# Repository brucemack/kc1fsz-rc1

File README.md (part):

Overview
========

This is a basic two-radio repeater controller that can be used 
to create an amateur or GMRS repeater site. Our goal is to implement
as much of the repeater functionality in software as 
possible. For this reason, we call this the "Software 
Defined Repeater Controller" (SDRC) project. This Github
repo contains the source code for the controller and the 
KiCad design files for the hardware.

The hardware is on two boards. The radio interface board is on the left
and the digital control board is on the right. The digital control board
is mostly a Pico Pi 2. (To avoid any confusion: the Pico is an ARM Cortex-M33 microcontroller. This _is not_ a Linux system like you'd find on a full 
a Raspberry Pi single-board computer).

One of the advantages of an all-digital architecture is that integration
with other digital-voice technologies should be seamless. Please
see the related project called [MicroLink](https://github.com/brucemack/microlink) which
provides a compact EchoLink implementation. Soon the SDRC and MicroLink
systems will be integrated. Reverse-engineering of the D-Star/DMR protocols
will also enable direct integration of those modes at some point. 

Much of the hardware used in traditional analog repeater controller 
designs
(analog cross-point switches, FPGAs, custom DTMF/CTCSS tone detection chips, 
digital voice CODECs, voice delay modules, M7716 noise squelch ICs, AGC circuits, etc.) will not be necessary
if these functions can be performed in software.

A [users guide is provided here](docs/users.md).

The SDRC system was developed by Bruce MacKinnon (KC1FSZ) with extensive design 
input from Dan Brown (W1DAN) of the Wellesley Amateur Radio Society (W1TKZ).
Please reach out with any questions/suggestions.

Capabilities
============

This repeater controller development is in process. The prototype is undergoing bench testing at the moment. We plan to install it at our W1TKZ repeater site within the next month.

Key capabilities of the software so far:

* Support for two receivers and two transmitters. Radios
can operate independently or can be linked to support
remote receiver or cross-band repeater operation.
* Hardware COS and CTCSS inputs for each radio. Positive
and negative logic are supported.
* An optically-isolated hardware PTT output for each radio.
* Optional soft CTCSS (PL) tone encoding and decoding, with support 
for independent tone frequencies for each transmitter/receiver.
* Optional noise squelch using a bi-level system similar to 
the Motorola M7716 IC.
* CW-ID generation.
* Configurable hang time.
* Configurable courtesy tone generation.
* Timeout and lockout with configurable times.
* Optional digital voice ID and other prompts.
* Soft RX/TX gain control adjustable remotely.
* <=250ms digital audio delay to avoid squelch tails.
* Optional AGC control with configurable level target, gain limits, 
and attack/decay parameters.
* Soft DTMF decoding, with password-protected remote commands.
* "Soft console" via USB-connected computer computer with
serial terminal provides a configuration shell and live display of the following:
  - Carrier detect (COS) status
  - PL tone detect (CTCSS) status
  - Push-to-talk (PTT) status
  - Receive/transmit audio level RMS and peak
* Microcontroller uses a watchdog timer to limit the risk of lockup.
* (In development) Remote firmware update via LoRa connection.

Other things to know:

* The audio output range is around 1.25Vpp into 600 ohms.
* The the receiver discriminator input is high impedance.
* Hardware gain adjustments (pots) are used to calibrate dynamic range 
during initial installation.
* The controller runs on +12VDC power input.
* A DB25 connection is used for radio interfaces.
* Over-voltage protection is provided on the audio and logic inputs.
* Over-voltage, reverse-polarity, and transient spike protection is provided
on the power input.

Hardware specs:

* Microcontroller is the RP2350 running at 125 MHz.
* ADC/DACs run at 32k samples/second with 24-bits of
resolution which is more than enough for an analog FM repeater.
* Low-noise op amps are used for audio scaling (TLV9152).
* During testing of the prototype board it was determined that the 
controller consumes ~105mA when idling and ~135mA when repeating. These are
fairly low current consumptions that indicate the the controller may 
be relevant in solar/battery installations.

More documentation:

* A demonstration video of the current prototype 
[can be seen here](https://www.youtube.com/watch?v=HBwrpokd7FI).
* A demonstration video of the soft console [can be seen here](https://www.youtube.com/watch?v=gWjOw0UzMgY).
* The schematic for the main radio interface board [is here](https://github.com/brucemack/kc1fsz-rc1/blob/main/hw/if-2/plots/if-2.pdf).
* The schematic for the microcontroller board [is here](https://github.com/brucemack/kc1fsz-rc1/blob/main/hw/digital-2/plots/digital-2.pdf).
* The hardware project for the LoRa integration [is here](https://github.com/brucemack/lora-r2).
* The software project for the LoRa integration [is here](https://github.com/brucemack/remote-probe).

Credit/Thanks
=============

I've received help from a lot of smart people on this project who have been very generous with their time:

* Dan Brown W1DAN, former president of the Wellesley Club.
* Tom Kinahan N1CPE, trustee of the W1TKZ repeater system.
* Leandra MacLennan AF1R
* Steve Kondo K1STK
* George Zafiropoulos KJ6VU. Among other things, George [sells his own commercial repeater controllers](https://www.packtenna.com/repeaters.html#/). 
* Jim Aspinwall NO1PC.  Jim is very experienced with repeaters and has engineered/maintained several multi-site systems. His [website is very interesting](https://www.no1pc.org/).
* Jeff Otterson (N1KDO), of [NHRC Repeater Controller](https://www.nhrc.net/). 

Legal/License
=============

This work is being made available for non-commercial use by the amateur radio community. Redistribution, commercial use or sale of any part is prohibited.

The hardware for this project is published under the terms of [The TAPR Open Hardware License](https://tapr.org/the-tapr-open-hardware-license).

The software for this project is published under the terms of [GNU GENERAL PUBLIC LICENSE](https://www.gnu.org/licenses/gpl-3.0.en.html).

Technical/Design Notes
======================

Typical Radio Audio Levels and Impedance 
----------------------------------------

I got these comments from an experienced expert:

> ... we usually run the internal audio at a nominal 1v p/p for full system deviation.  That seems to have worked fine.  At the edges you may need more of a voltage swing especially on the output depending on the transmitter you are driving but this covers 90%++ of the cases.

> Discriminator / modulator audio inputs are never 600 Ohms.  The output impedance of the receiver is higher.  Often 5k to 10k Ohms, the modulator inputs are typically low impedance which is fine for an op amp output.  Both unbalanced.

Op Amp Notes
------------

* [TLV9152](https://www.ti.com/lit/ds/symlink/tlv9152.pdf?ts=1750522536760) - Suggested by Dan, output rail-to-rail. This is the part that is in the current design.
* [TL072]() - Output to within +/- 1.5V (typ) of rail. A good part,
but very old. Used in initial prototypes.
* [LMC660](https://www.ti.com/lit/ds/symlink/lmc662.pdf) - Used in SCOM-7K, output rail-to-rail, can drive +/- 18mA.  Characterized as 4.6 to 0.3 output swing with R<sub>L</sub> = 600 ohms. A quad device, not a good choice.
* [TS952](https://www.st.com/content/ccc/resource/technical/document/datasheet/b8/ac/21/72/20/a7/4d/ea/CD00001338.pdf/files/CD00001338.pdf/jcr:content/translations/en.CD00001338.pdf) - Used in the SCOM 7330, output close to rail-to-rail with R<sub>L</sub> = 600 ohms.
* [TLV2462](https://www.ti.com/lit/ds/symlink/tlv2462-q1.pdf?ts=1750512090542) - Output rail-to-rail, can drive +/- 80mA. Noise 11nV/RHz.

Zener Biasing for Single Supply Op Amps
---------------------------------------

From [Analog Devices application note AN-581](https://www.analog.com/en/resources/app-notes/an-581.html):

A Zener should be chosen that has an operating voltage close to Vs/2. Resistor RZ needs to be selected to provide a high enough Zener current to operate the Zener at its stable rated voltage and to keep the Zener output noise low. It is also important to minimize power consumption (and heating) and to prolong the life of the Zener. As the op amp’s input current is essentially zero, it’s a good idea to choose a low power Zener. A 250 mW device is best but the more common 500 mW types are also acceptable. The ideal Zener current varies with each manufacturer but practical IZ levels between 5 mA (250 mW Zener) and 5 µA (500 mW Zener) are usually a good compromise for this application.

Overview of Digital Audio Flow
------------------------------

This diagram shows the flow between one receiver and one
transmitter. Keep in mind that multiple instances of 
this flow are running in parallel for each receiver/transmitter
pair. Furthermore, transmit audio can select/mix from
any of the receivers.

The letters in the diagram above will be referenced throughout.

Generation of I2S Clock/State Machines
--------------------------------------

The PICO PIO (programmable IO) feature has been leveraged
to generate the I2S clock lines and internal state machines.
To save GPIO pins, the same I2S clocks (SCLK, BCLK, LRCLK) are 
shared by the ADC **and** DAC chips.  

Analog to Digital Conversion
----------------------------

The ADC is a TI PC1804 (Flow diagram ref A). This was selected 
because of its simplicity,
availability, and ease of soldering. This is a 24 bit converter
so full scale runs from +/- 8,388,608. The digital interface 
is I2S.

The converter supports a range of conversion rates from 32k
to 192k.  The lowest possible rate has been selected for this
project.

This converter IC has two important filters built-in:
* A low-pass
anti-aliasing filter with a cutoff frequency of f<sub>s</sub>/2.
* A high-pass filter just above 0Hz for DC removal. Testing
has shown that this filter is sharp and doesn't attenuate
the very low audio frequencies used for CTCSS/PL tones.

Decimation From 32k to 8k Audio
-------------------------------

The ADC runs at a sample rate of 32k.  In order to 
reduce memory and CPU requirements the audio stream is down-sampled
to 8k (decimation by 4). See flow diagram reference C and D. 
Following the decimation,
audio processing in the rest of the flow will run at 8k.

This decimation happens in two ÷2 steps. Each decimation step
also includes a half-band LPF so the decimation has 
the effect of band-limiting the audio to 4kHz.

The design process for creating these half-band low-pass
decimation filters is very standard. A detailed discussion 
can be found in section 5.3 (first ed) of the Lyons DSP book.

The cut-off frequency of the first decimation is 8kHz and the 
second is 4kHz.  However, the f<sub>s</sub> of the first 
filter is twice the second so the same filter coefficients
can be used for both decimation steps. I am using a 41-tap 
filter for this process because the transition doesn't need
to be extremely sharp.

Receiver CTCSS/PL Tone Filtering
---------------------------------

The received CTCSS/PL tone needs to be filtered away so that it 
isn't repeated.  This is particularly
important for cross-band repeaters where the *PL tone might 
be different* on the two sides of the repeater.
"Pass-through" CTCSS tone is not desired. If the CTCSS encoder 
is enabled the appropriate tone will be synthesized and added
back to the transmitted signal on the way out.

A [commercial high-pass filter for CTCSS rejection](https://www.masterscommunications.com/products/filter/plf15.html) created by K3KKC and characterized in this
[review by WA1MIK](https://www.masterscommunications.com/products/filter/fl10-eval/fl10-evaluation.html) includes some specifications that can be 
used to guide the design. This filter has a 350Hz 
-3dB frequency and 30dB per octave of steepness.  That's down 
about -68dB at 50Hz. There is a response curve provided
in the WA1MIK article.

K3KKC's filter is analog, but this is a software-defined controller so 
I am replicating this filter behavior using a digital FIR filter 
that is synthesized using the "optimal" (Parks McClellan) algorithm. 
I'm going to assume the transition band starts at 200 Hz (i.e. the 
end of the stop band) and ends at 350 Hz (i.e. the start of the 
pass band). See flow diagram reference F.

We can estimate the number of taps required to perform this
filtering task 
using the so-called "Harris Approximation" (see *Multirate Signal Processing for Communication Systems*, Fredric J. Harris, 2004, page 216, equation (8.16)).

taps = (f<sub>s</sub> / Δf) * (dB<sub>att</sub> / 22)

where dB<sub>att</sub> is the desired attenuation of the stopband
and Δf is the desired width of the transition band.

Using Δf of (375-200) = 175 Hz and dB<sub>att</sub> of 
-68dB, we end up with a requirement of about 141 taps. Unfortunately,
it turns out that my [Parks McClellan implementation](https://github.com/brucemack/firpm-py) is limited to 127 taps at the moment, so
we'll just assume that is close enough. I'll fix that later
if it seems like this matters.

The group-delay of an FIR filter is approximately:

samples<sub>delay</sub> = (N - 1) / 2 

So this filter introduces about 8ms of delay into the system.

Here's a plot of the frequency response of the 127-tap filter
created by the PM algorithm created using Matplotlib:

As a sanity check I ran a 200 Hz tone through the
synthesized filter (amplitude 
1.0) and plotted the output. The amplitude of the output is about 0.0025,
or about -52dB, so things look pretty good on the low end of the
transition band.

As another sanity check I ran a 350 Hz tone through the same
filter and plotted the output. The amplitude is about 0.9, or about 
-0.9dB, so the high end of the transition is looking reasonable as
well.

This 127 tap filter should work fine for the purposes of CTCSS
filtering.

CTCSS Tone Decoder
------------------

See flow diagram reference G.

This is a fairly straight-forward tone detection problem. The 
digital [Goertzel algorithm](https://en.wikipedia.org/wiki/Goertzel_algorithm) is
used to efficiently detect the configured tone in firmware.
Configurable debounce times are used to prevent false triggers
and false drops of the detector.

The algorithm has been tested to ensure sharpness of the 
detection filter. The filter was set to detect the PL 
tone of 123 Hz (W1TZK VHF tone) and a range of tones (plus a 
high level of additive white Gaussian noise) were played
into the filter. The response is charted below. 

One challenge creating a narrow tone detector using the 
Goertzel algorithm is making sure that we are using 
enough samples to provide sufficient frequency resolution.
On the other hand, we want to make sure to provide some 
tolerance for transmitters that are off a bit in their 
PL tone synthesis.

The width of a frequency bucket using any DFT-based 
analysis method is:

BW<sub>bin</sub> = f<sub>s</sub> / samples

The current implementation is using 512 samples (8x 8ms blocks),
which implies a resolution bandwidth of about 15Hz. This also 
implies that the "attack" time of the CTCSS decoder
is about 64ms.

Demonstration Files of My CTCSS Detector Implementation
-------------------------------------------------------

I've created a demonstration of the soft CTCSS decoder in 
action. I've made a 7 second sample clip that consists of 
three parts:
* 2 seconds of white noise
* 3 second of voice audio with a 123 Hz PL tone added (-20dB),
low-pass filtered to 2.3kHz.
* 2 seconds of white noise

The first clip is here: [Sound 2](https://github.com/brucemack/kc1fsz-rc1/raw/refs/heads/main/docs/clip-2.wav). This
is the raw sample.  As expected, you
hear the noise before and after the voice audio - the 
CTCSS tone is ignored. If you listen closely to this clip 
you can also hear the 123 Hz tone under the voice audio. 

The second sound clip is here: [Sound 2b](https://github.com/brucemack/kc1fsz-rc1/raw/refs/heads/main/docs/clip-2b.wav). This
is the sample played through the controller firmware 
with the CTCSS decoder enabled and the CTCSS high-pass filter enabled. Here the noise is blocked
except for a short tail at the end of the voice. The decoder takes about
32ms (around 4 cycles of the PL tone) to determine that 
the tone has stopped. The noise is blocked and the PL 
tone is filtered out. This is close to what we would expect 
a "real" system to sound like.

This test was repeated with the PL tone under the 
voice section of the clip down another 
-6dB for a total of -26dB relative to full-scale (0.05 
amplitude in linear units).  The original clip is here: [Sound 3](https://github.com/brucemack/kc1fsz-rc1/raw/refs/heads/main/docs/clip-3.wav) and the clip played through the controller firmware 
with CTCSS decoder and CTCSS HPF enabled is here: [Sound 3b](https://github.com/brucemack/kc1fsz-rc1/raw/refs/heads/main/docs/clip-3b.wav).

CTCSS Tone Encoder
------------------

See flow diagram reference J. The digital CTCSS generator runs in 
the 8kHz part of the audio flow. Each radio has its
own encoder frequency to support multi-tone systems.

Dan suggested that the goal should be to create a PL tone modulated at about 10% total deviation. If we assume that CW/courtesy tones are generated at a level of between
-14dB and -10dB of full DAC full scale, the PL tone should be 
another -12dB down, or 0.32 * 0.25 = 0.08 linear scale.

Here's a clip with the CTCSS encoder enabled (123 Hz) and 
set to a high 
level (-20dB) so it can be heard: [Sound 3d](https://github.com/brucemack/kc1fsz-rc1/raw/refs/heads/main/docs/clip-3d.wav).

Here's a view of the spectrum with the CTCSS encoder enabled
at 123 Hz under an audio clip:

CW Generator
------------

See flow diagram reference K.

This component is used to generate tones for CW-ID and the 
courtesy tones. Envelope shaping is used to avoid high 
frequency glitches associated with on/off keying.

Voice Synthesis
---------------

See flow diagram reference K.

To reduce storage, voice prompts are compressed using the 
GSM 0610 full-rate CODEC. [I created a fixed-point implementation](https://github.com/brucemack/gsm-0610-codec) of 
this CODEC as part of my [Echolink Implementation](https://github.com/brucemack/microlink). GSM 0610 runs at 8k so this 
is a smooth integration. 

One second of audio requires 8K of flash storage (640 byte
frames transferred at 12.5 frames/second). About
512K of flash has been allocated to voice storage, so 
we've got room for about 60 seconds of recording.

(More to be documented)

Noise Squelch IC From Motorola
------------------------------

Not all radios have access to a reliable COS signal and some 
radios may have inferior noise squelches. There are a few 
ways to deal with this. Jim NO1PC made me aware of an 
interesting component introduced in the Motorola MICOR stations of 
the 1970's to address this challenge. 

The goal of these circuits is to identify the end of a 
transmission as quickly as possible and to squelch (mute) the 
transmitter before the "static crash" is broadcast. If this
detection can be made quickly enough we can avoid the need
to create delayed versions of the receive audio stream.
More on the topic of delay is provided in a later section.

It turns out that Motorola created a custom IC to address
this need.  The IC is called either the M7716 or the M6709, 
or sometimes the SC7716. The IC implements something called
"switched hysteresis squelch."

The Repeater Builder site has a few different articles that 
go into the details of this chip.
* [This article by WAØAUQ](https://www.repeater-builder.com/micor/micor-bi-level-squelch-circuit.html) gives a good overview.
* [This article by W3KKC](https://www.repeater-builder.com/micor/micor-bi-level-squelch-theory.html) also provides some theory.
* [The most detailed article is by Robert W. Meister WA1MIK](https://www.repeater-builder.com/micor/m6709-info/m6709-info.html). Robert
has done a reverse engineering of the chip in order to quantify 
it's behavior.

Quoting from WA1MIK's analysis, a _"noise squelch systems must ignore signals in the voice frequency range of about 300 to 3400 Hz. All of the high-pass filtering is designed to eliminate any voice energy and only look at the noise energy above 
about 5 kHz."_ Conceptually, a "quieted" FM channel would contain 
most of its energy concentrated in the voice band, whereas noise is broadband. 

And from W3KKC's article: _"If the received quality of the input 
signal provides at least 20 dB quieting, (above 1 uV on properly 
working receiver), the IC's logic circuit gives immediate audio 
shut-off, and no squelch tail. If the signal is below 20 dB 
quieting, (below 1 uV, or having some noise), there is a squelch 
tail of 150 milliseconds, long enough so there is no audio 
chopping under "flutter" conditions ..."_. The chart entitled "M6709 Squelch Tail Threshold" in the WA1MIK analysis article summarizes 
this bi-level behavior on the squelch tail.

There are a few things that I'm assuming from these articles, 
although not explicitly stated:

* When the articles talk about "20dB of quieting," I'm pretty
sure this is referring to a measurement of the ratio between 
the voice-band energy (<4kHz) to the above-voice-band energy (>5kHz). Since there is always output coming from an FM discriminator, the 
only way to determine
if that discriminator output is a signal is to determine 
when the noise part of the spectrum has quieted down sufficiently.
* From the WA1MIK tail threshold chart, I am assuming that 
the 10dB of quieting is the threshold for opening the squelch.
* The articles use the term "hysteresis" when describing 
the M7716's functionality. It's not explicitly stated where
the hysteresis loop manifests itself. I am assuming that this
is referring to the fact that the mute to unmute transition 
is immediate but the unmute to mute 
transition is delayed by 150ms (configurable) in the case that a <20dB quieted
signal is lost.
* For example, I am assuming that a transition from 9dB of 
quieting to 21dB and back to 9dB
would result in the squelch immediately opening and
then immediately closing, without delay or asymmetry.
* I am also assuming that if the signal goes above 10dB at any 
time during
the 150ms delay period that the delay counter is reset and
will start to count down again once the signal dips below
10dB of quieting again.

Technical Notes on My Implementation of a Noise Detector
--------------------------------------------------------

Given the theory about the M7716 above, we need to have
a measure of the noise energy present in an input signal.
This is a place where having an overly-wide (32kHz) ADC 
sampling rate is a good thing. 

A high-pass filter is used to extract the energy above
5kHz (see flow diagram reference B). Assuming the transition 
band of this filter starts 
at 4kHz and ends at 6kHz and -30dB of attenuation is 
sufficient, the Harris Approximation tells us to use a 
21-tap FIR filter.

This FIR filter runs directly on the 32kHz sampled
audio from the ADC. Every 10ms an RMS level is computed
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
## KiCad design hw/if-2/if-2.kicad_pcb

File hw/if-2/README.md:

## Audio Input Network Simulation

Simulated audio input network. The trim pot is set to half range.

Frequency response. We are using an ADC with a differential input so a differential gain is plotted:

Frequency response focusing on the range from 60 Hz to 2 kHz. This range is important since we will
be decoding sub-audible CTCSS tones and we want to make sure they are passed into the ADC. The lowest
tone (66 Hz) is only attenuated by about 0.3 dB vs the audible range starting at 200 Hz.

## Audio Output Network Simulation

This is the final filter in the audio output chain. The trim pot is set to half range. A low-pass network is used to suppress noise. This is not used for pre-/de-emphasis.

CTCSS tones need to pass through this network so very low frequency response is necessary.

The gain is provided in case the full-scale DAC amplitude isn't enough to drive the audio input of the radio.  

Simulated audio output network (stage 2):

Frequency response:

Frequency response focusing on the range from 60 Hz to 2 kHz. The lowest tone is only attenuated by about 0.6 dB vs. the audible range. This should be fine.

## ADC Testing at Low Audio Frequency

(To Follow)

## DAC Testing at Low Audio Frequency

(To Follow)

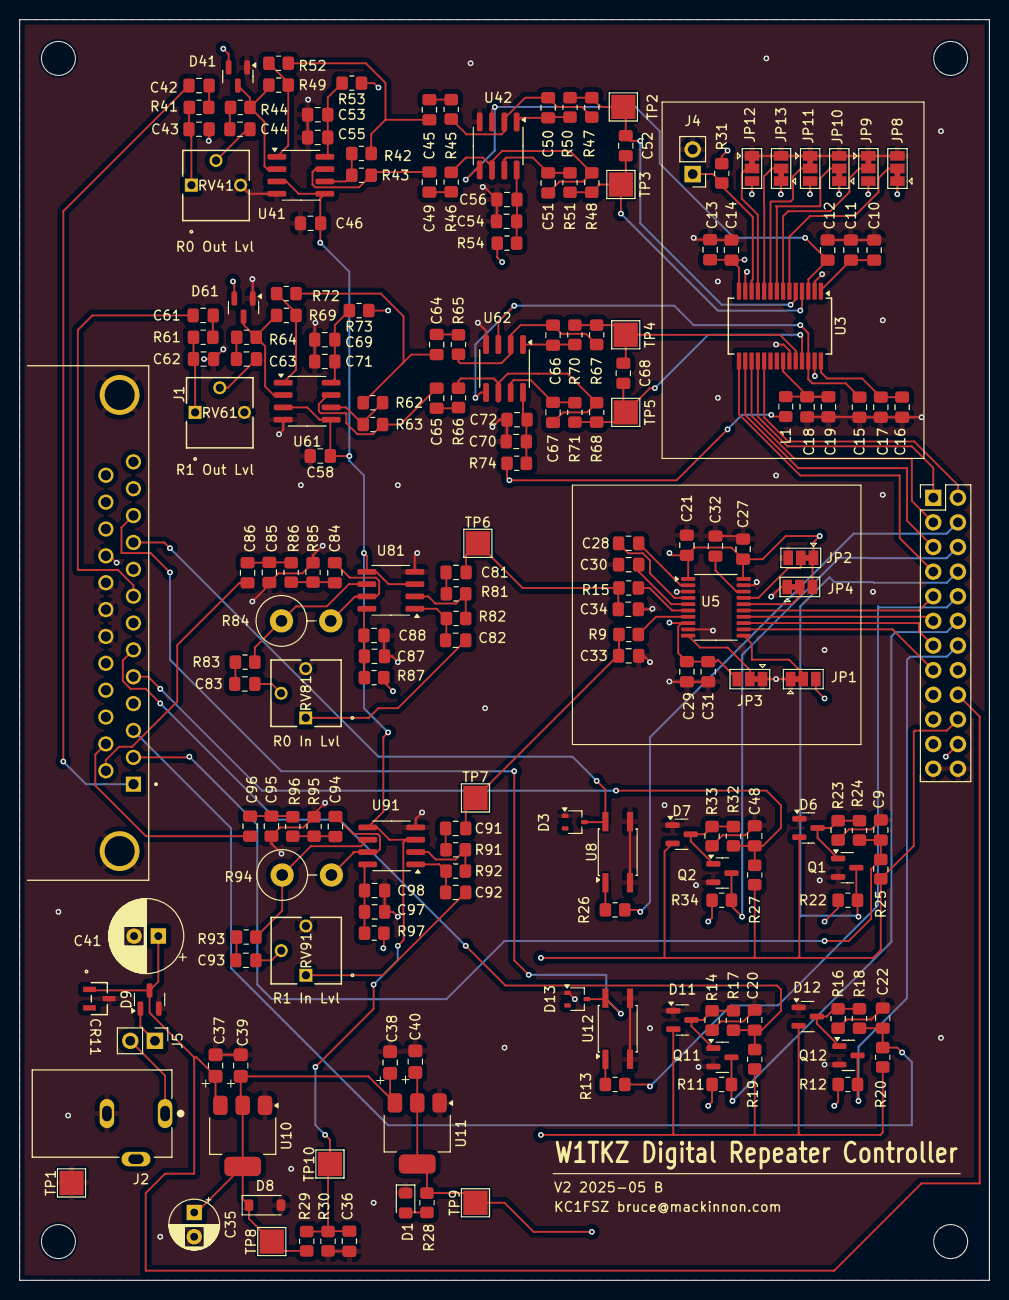
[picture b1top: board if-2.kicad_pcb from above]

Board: 4 copper layers, 100.0 x 130.0 mm, 200 parts (0 on the bottom side), 123 nets.

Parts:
C9, C20, C22, C48, C85, C95: 100p; C_0805_2012Metric_Pad1.18x1.45mm_HandSolder
C10, C12, C15, C16, C46, C58: 1u; C_0805_2012Metric_Pad1.18x1.45mm_HandSolder
C11, C14, C17, C19, C88, C98: 0.1u; C_0805_2012Metric_Pad1.18x1.45mm_HandSolder
C13, C18, C31, C36, C53, C54, C69, C70, C87, C97: 10u; C_0805_2012Metric_Pad1.18x1.45mm_HandSolder
C21, C27, C29, C32: 0.1uF; C_0805_2012Metric_Pad1.18x1.45mm_HandSolder
C28, C30: 2.2uF; C_0805_2012Metric_Pad1.18x1.45mm_HandSolder
C33, C34: 2.2nF; C_0805_2012Metric_Pad1.18x1.45mm_HandSolder
C35: 100uF; CP_Radial_D5.0mm_P2.50mm
C37, C38, C39, C40: 10u; CPOL_0805_2012Metric_Pad1.18x1.45mm_HandSolder
C41: 470u; CP_Radial_D7.5mm_P2.50mm
C42, C44, C45, C49, C61, C63, C64, C65, C81, C82, C83, C91, C92, C93: 4.7u; C_0805_2012Metric_Pad1.18x1.45mm_HandSolder
C43, C62: 0.001u; C_0805_2012Metric_Pad1.18x1.45mm_HandSolder
C50, C51, C66, C67: 1800p; C_0805_2012Metric_Pad1.18x1.45mm_HandSolder
C52, C68: 0.01u; C_0805_2012Metric_Pad1.18x1.45mm_HandSolder
C55, C56, C71, C72: 01.u; C_0805_2012Metric_Pad1.18x1.45mm_HandSolder
C84, C86, C94, C96: 10uF; C_0805_2012Metric_Pad1.18x1.45mm_HandSolder
CR11: ESDA14V2LY; SOT23-3L_STM
D1: Red; LED_0805_2012Metric_Pad1.15x1.40mm_HandSolder
D3, D13: BAT54W; SOT-323_SC-70
D6, D7, D11, D12, D41, D61: BAT54S; SOT-23
D8: 5.1V; D_SOD-123
D9: BAT54C; SOT-23
H1, H2, H3, H4: MountingHole; MountingHole_3.5mm
J1: DB25_Socket; AMPHENOL_L77SDB25SA4CH4F
J2: PJ-102AH; Power_5.5mm_CUI_PJ-102AH
J3: Conn_02x12_Odd_Even; PinHeader_2x12_P2.54mm_Vertical
J4, J5: Conn_01x02; PinHeader_1x02_P2.54mm_Vertical
JP1, JP2, JP3, JP4, JP8, JP9, JP10, JP11, JP12, JP13: SolderJumper_3_Bridged12; SolderJumper-3_P1.3mm_Bridged12_Pad1.0x1.5mm
L1: 47u; L_0805_2012Metric_Pad1.15x1.40mm_HandSolder
Q1, Q2, Q11, Q12: MMBT3904; SOT-23
R9, R15: 470; R_0805_2012Metric_Pad1.20x1.40mm_HandSolder
R11, R12, R22, R34: 2.2k; R_0805_2012Metric_Pad1.20x1.40mm_HandSolder
R13, R26: 200; R_0805_2012Metric_Pad1.20x1.40mm_HandSolder
R14, R16, R19, R20, R23, R25, R27, R31, R33, R42, R43, R62, R63: 4.7k; R_0805_2012Metric_Pad1.20x1.40mm_HandSolder
R17, R18, R24, R29, R30, R32, R85, R95: 10k; R_0805_2012Metric_Pad1.20x1.40mm_HandSolder
R28: 100; R_0805_2012Metric_Pad1.20x1.40mm_HandSolder
R41, R45, R46, R47, R48, R52, R61, R65, R66, R67, R68, R72: 1k; R_0805_2012Metric_Pad1.20x1.40mm_HandSolder
R44, R64, R81, R82, R83, R91, R92, R93: 20k; R_0805_2012Metric_Pad1.20x1.40mm_HandSolder
R49, R69: 100k; R_0805_2012Metric_Pad1.20x1.40mm_HandSolder
R50, R51, R53, R54, R70, R71, R73, R74, R87, R97: 47; R_0805_2012Metric_Pad1.20x1.40mm_HandSolder
R84, R94: 100k; R_Axial_DIN0516_L15.5mm_D5.0mm_P5.08mm_Vertical
R86, R96: 510; R_0805_2012Metric_Pad1.20x1.40mm_HandSolder
RV41, RV61, RV81, RV91: 50k; POT_3362P
TP1, TP2, TP3, TP4, TP5, TP6, TP7, TP8, TP9, TP10: TestPoint; TestPoint_Pad_2.5x2.5mm
U3: PCM1804DBR; SSOP-28_5.3x10.2mm_P0.65mm
U5: PCM5100; TSSOP-20_4.4x6.5mm_P0.65mm
U8, U12: LTV-356T; SO-4_4.4x3.6mm_P2.54mm
U10: NCP1117-5.0_SOT223; SOT-223-3_TabPin2
U11: NCP1117-3.3_SOT223; SOT-223-3_TabPin2
U41, U42, U61, U62, U81, U91: TL072; SOIC-8_3.9x4.9mm_P1.27mm

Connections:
12V_UNFUSED: J2.1, J5.2
+3.3V: C13.1, C14.1, C21.1, C27.1, C29.1, C31.1, C40.1, J3.22, JP1.3 (B), JP2.1 (A), JP3.3 (B), JP4.3 (B), JP8.1 (A), JP9.3 (B), JP10.1 (A), JP11.3 (B), JP12.3 (B), JP13.1 (A), R11.1, R12.1, R22.1, R28.1, R31.1, R34.1, TP9.1, U3.14 (VDD), U5.1 (CPVDD), U5.8 (AVDD), U5.20 (DVDD), U11.2 (VO)
+5V: C35.1, C38.1, C39.1, D6.2 (K), D7.2 (K), D8.1 (K), D11.2 (K), D12.2 (K), D41.2 (K), D61.2 (K), J3.20, L1.1, R19.1, R20.1, R25.1, R27.1, R29.1, R53.1, R54.1, R73.1, R74.1, R87.2, R97.2, TP8.1, U10.2 (VO), U11.3 (VI)
+12V: C37.1, C41.1, CR11.1, D9.3, J3.18, U10.3 (VI)
ADC_BCK: J3.5, U3.16 (BCK/DSDL)
ADC_DOUT: J3.7, U3.15 (DATA/DSDR)
ADC_HPFBYPASS: J4.1, R31.2, U3.12 (BYPAS)
ADC_LRCK: J3.3, U3.17 (LRCK/DSDBCK)
ADC_SCK: J3.1, U3.18 (SCKI)
DAC_BCK: J3.13, U5.13 (BCK)
DAC_DIN: J3.11, U5.14 (DIN)
DAC_LRCK: J3.9, U5.15 (LRCK)
DAC_SCK: J3.15, U5.12 (SCK)
DEMP: JP3.2 (C), U5.10 (DEMP)
FLT: JP1.2 (C), U5.11 (FLT)
FMT: JP4.2 (C), U5.16 (FMT)
FMT0: JP8.2 (C), U3.6 (FMT0)
FMT1: JP9.2 (C), U3.7 (FMT1)
GND: C9.2, C10.2, C11.2, C12.2, C13.2, C14.2, C15.2, C16.2, C17.2, C18.2, C19.2, C20.2, C21.2, C22.2, C27.2, C29.2, C30.2, C31.2, C32.2, C33.2, C34.2, C35.2, C36.2, C37.2, C38.2, C39.2, C40.2, C41.2, C43.2, C46.2, C48.2, C53.2, C54.2, C55.2, C56.2, C58.2, C62.2, C69.2, C70.2, C71.2, C72.2, C85.2, C87.2, C88.2, C95.2, C97.2, C98.2, CR11.3, D1.1 (K), D3.1 (A), D6.1 (A), D7.1 (A), D8.2 (A), D9.2, D11.1 (A), D12.1 (A), D13.1 (A), D41.1 (A), D61.1 (A), J1.19, J1.20, J1.21, J1.22, J1.SH1 (Shell), J1.SH2 (Shell), J2.2, J3.23, J3.24, J4.2, JP1.1 (A), JP2.3 (B), JP3.1 (A), JP4.1 (A), JP8.3 (B), JP9.1 (A), JP10.3 (B), JP11.1 (A), JP12.1 (A), JP13.3 (B), Q1.2 (E), Q2.2 (E), Q11.2 (E), Q12.2 (E), R14.2, R16.2, R23.2, R30.2, R33.2, R85.2, R95.2, RV41.3, RV61.3, RV81.3, RV91.3, TP1.1, U3.2 (AGNDL), U3.13 (DGND), U3.23 (AGND), U3.27 (AGNDR), U5.3 (CPGND), U5.9 (AGND), U5.19 (DGND), U8.2, U8.3, U10.1 (GND), U11.1 (GND), U12.2, U12.3, U41.4 (V-), U42.4 (V-), U61.4 (V-), U62.4 (V-), U81.4 (V-), U91.4 (V-)
unnamed: C42.2, R41.1
unnamed: C43.1, R41.2, RV41.1
unnamed: C44.1, R44.1
unnamed: C44.2, RV41.2
unnamed: C45.1, R42.1, R52.2
unnamed: C45.2, R45.1
unnamed: C49.1, R43.2, U41.7
unnamed: C49.2, R46.1
unnamed: C50.2, R50.1, U42.1
unnamed: C51.2, R51.1, U42.7
unnamed: C61.2, R61.1
unnamed: C62.1, R61.2, RV61.1
unnamed: C63.1, R64.1
unnamed: C63.2, RV61.2
unnamed: C64.1, R62.1, R72.2
unnamed: C64.2, R65.1
unnamed: C65.1, R63.2, U61.7
unnamed: C65.2, R66.1
unnamed: C66.2, R70.1, U62.1
unnamed: C67.2, R71.1, U62.7
unnamed: C81.2, R81.1
unnamed: C82.1, R82.2, U81.1
unnamed: C82.2, RV81.1
unnamed: C83.1, RV81.2
unnamed: C83.2, R83.1
unnamed: C84.1, R84.2, U81.7
unnamed: C84.2, R85.1, R86.1
unnamed: C85.1, C86.1, R86.2
unnamed: C91.2, R91.1
unnamed: C92.1, R92.2, U91.1
unnamed: C92.2, RV91.1
unnamed: C93.1, RV91.2
unnamed: C93.2, R93.1
unnamed: C94.1, R94.2, U91.7
unnamed: C94.2, R95.1, R96.1
unnamed: C95.1, C96.1, R96.2
unnamed: D1.2 (A), R28.2
unnamed: D6.3 (COM), Q1.1 (B), R23.1, R24.2
unnamed: D7.3 (COM), Q2.1 (B), R32.2, R33.1
unnamed: D11.3 (COM), Q11.1 (B), R14.1, R17.2
unnamed: D12.3 (COM), Q12.1 (B), R16.1, R18.2
unnamed: D41.3 (COM), R44.2, R49.1, U41.2 (-)
unnamed: D61.3 (COM), R64.2, R69.1, U61.2 (-)
unnamed: D9.1, J5.1
unnamed: R13.2, U12.1
unnamed: R26.2, U8.1
unnamed: R49.2, R52.1, U41.1
unnamed: R69.2, R72.1, U61.1
unnamed: C18.1, C19.1, L1.2, U3.22 (VCC)
unnamed: C16.1, C17.1, U3.28 (VREFR)
unnamed: C28.2, U5.4 (CAPM)
unnamed: C28.1, U5.2 (CAPP)
unnamed: C32.1, U5.18 (LDOO)
unnamed: R15.2, U5.6 (OUTL)
unnamed: R9.2, U5.7 (OUTR)
unnamed: C30.1, U5.5 (VNEG)
unnamed: R42.2, R43.1, U41.6 (-)
unnamed: C53.1, C55.1, R53.2, U41.8 (V+)
unnamed: C50.1, R45.2, R47.1, U42.2 (-)
unnamed: C51.1, R46.2, R48.1, U42.6 (-)
unnamed: C54.1, C56.1, R54.2, U42.8 (V+)
unnamed: R62.2, R63.1, U61.6 (-)
unnamed: C69.1, C71.1, R73.2, U61.8 (V+)
unnamed: C66.1, R65.2, R67.1, U62.2 (-)
unnamed: C67.1, R66.2, R68.1, U62.6 (-)
unnamed: C70.1, C72.1, R74.2, U62.8 (V+)
unnamed: R81.2, R82.1, U81.2 (-)
unnamed: R83.2, R84.1, U81.6 (-)
unnamed: C87.1, C88.1, R87.1, U81.8 (V+)
unnamed: R91.2, R92.1, U91.2 (-)
unnamed: R93.2, R94.1, U91.6 (-)
unnamed: C97.1, C98.1, R97.1, U91.8 (V+)
OSR0: JP11.2 (C), U3.9 (OSR0)
OSR1: JP13.2 (C), U3.10 (OSR1)
OSR2: JP12.2 (C), U3.11 (OSR2)
R0_AUDIO_IN: C42.1, J1.1
R0_AUDIO_OUT: C86.2, J1.14
R0_COS: C9.1, J1.2, R24.1, R25.2
R0_COS_B: J3.8, Q1.3 (C), R22.2
R0_CTCSS: C48.1, J1.5, R27.2, R32.1
R0_CTCSS_B: J3.6, Q2.3 (C), R34.2
R0_PTT: D3.3 (K), J1.10, U8.4
R0_PTT_B: J3.4, R26.1
R0_VCOM: C12.1, U3.3 (VCOML), U42.3 (+), U42.5 (+)
R0_VIN+: C52.1, R48.2, R51.2, TP3.1, U3.4 (VINL+)
R0_VIN-: C52.2, R47.2, R50.2, TP2.1, U3.5 (VINL-)
R0_VOUT: C34.1, C81.1, R15.1, TP6.1
R1_AUDIO_IN: C61.1, J1.8
R1_AUDIO_OUT: C96.2, J1.15
R1_COS: C22.1, J1.3, R18.1, R20.2
R1_COS_B: J3.14, Q12.3 (C), R12.2
R1_CTCSS: C20.1, J1.6, R17.1, R19.2
R1_CTCSS_B: J3.12, Q11.3 (C), R11.2
R1_PTT: D13.3 (K), J1.11, U12.4
R1_PTT_B: J3.10, R13.1
R1_VCOM: C15.1, U3.26 (VCOMR), U62.3 (+), U62.5 (+)
R1_VIN+: C68.1, R68.2, R71.2, TP5.1, U3.25 (VINR+)
R1_VIN-: C68.2, R67.2, R70.2, TP4.1, U3.24 (VINR-)
R1_VOUT: C33.1, C91.1, R9.1, TP7.1
S/~M: JP10.2 (C), U3.8 (S/M)
VBIAS: C36.1, C46.1, C58.1, R29.2, R30.1, TP10.1, U41.3 (+), U41.5 (+), U61.3 (+), U61.5 (+), U81.3 (+), U81.5 (+), U91.3 (+), U91.5 (+)
VREFL: C10.1, C11.1, U3.1 (VREFL)
XSMT: JP2.2 (C), U5.17 (XSMT)
~ADC_RST: J3.2, U3.19 (~REST)

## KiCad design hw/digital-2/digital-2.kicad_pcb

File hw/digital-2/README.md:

Wiring Notes
============

Pico 2 Pinout:
* GP0  - (UART0 TX)
* GP1  - (UART0 RX)
* GP2  - I2C1 SDA for display and IO expander
* GP3  - I2C1 SCL for display and IO expander
* GP4  - I2S SCK out to PCM1804 ADC and PCM5100 DAC
* GP5  - RST out to PCM1804 ADC
* GP6  - I2S DIN in from PC1804 ADC
* GP7  - I2S BCK out to PC1804 ADC
* GP8  - I2S LRCK out to PC1804 ADC
* GP9  - I2S DOUT out to PCM5100 DAC
* GP10 - I2S BCK out to PCM5100 DAC
* GP11 - I2S LRCK out to PCM5100 DAC
* GP12 - R0 COS IN
* GP13 - R0 CTCSS IN
* GP14 - R0 PTT OUT
* GP15 - R1 COS IN
* GP16 - R1 CTCSS IN
* GP17 - R1 PTT OUT
* GP18 - R0 RX Indicator
* GP19 - R0 TX Indicator
* GP20 - R1 RX Indicator
* GP21 - R1 TX Indicator
* GP22 - User LED0
* GP25 - Integrated LED
* GP26 - User LED1
* GP27 - User Button0
* GP28 - User Button1

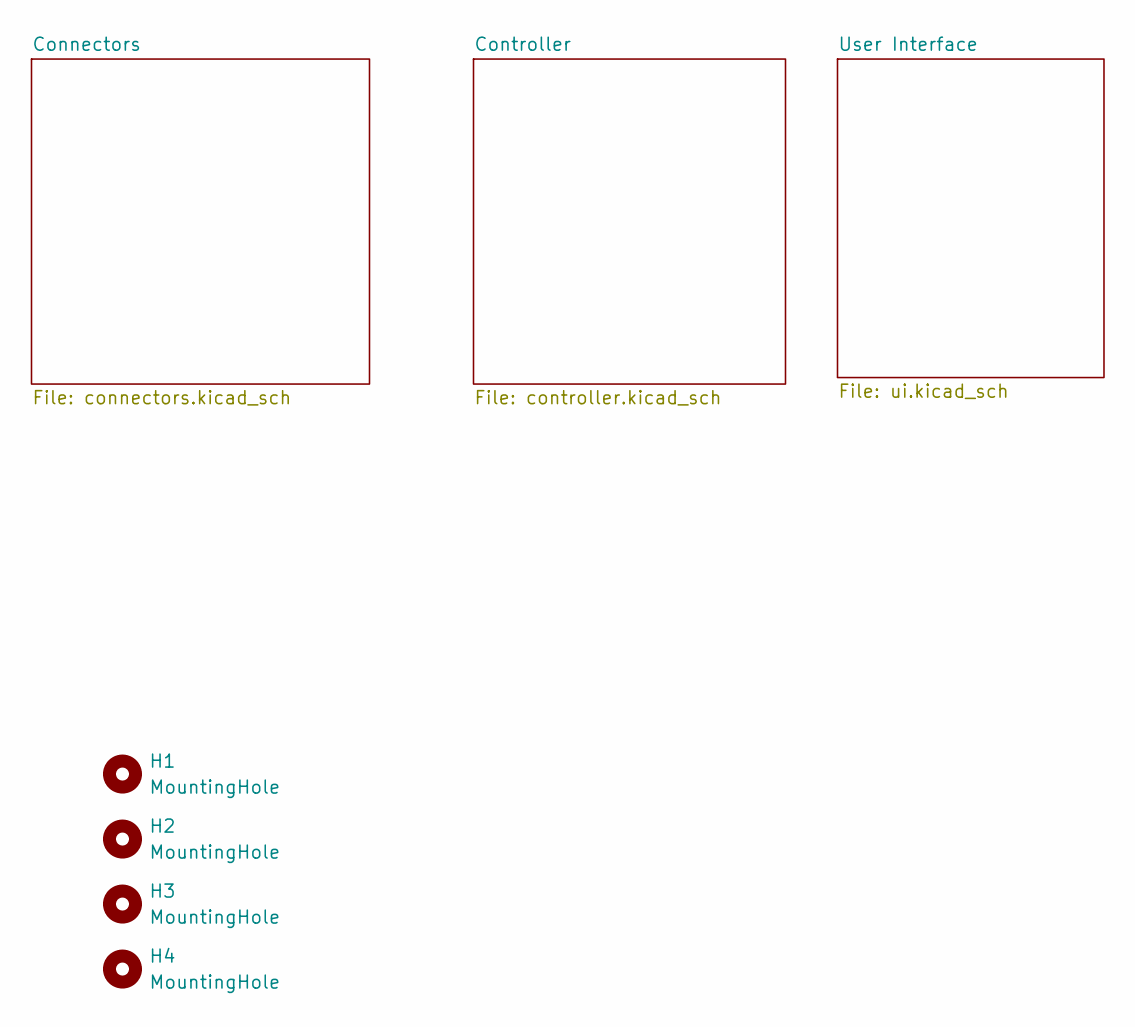
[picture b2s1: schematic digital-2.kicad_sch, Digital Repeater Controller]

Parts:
H1, H2, H3, H4: MountingHole; MountingHole_3.5mm

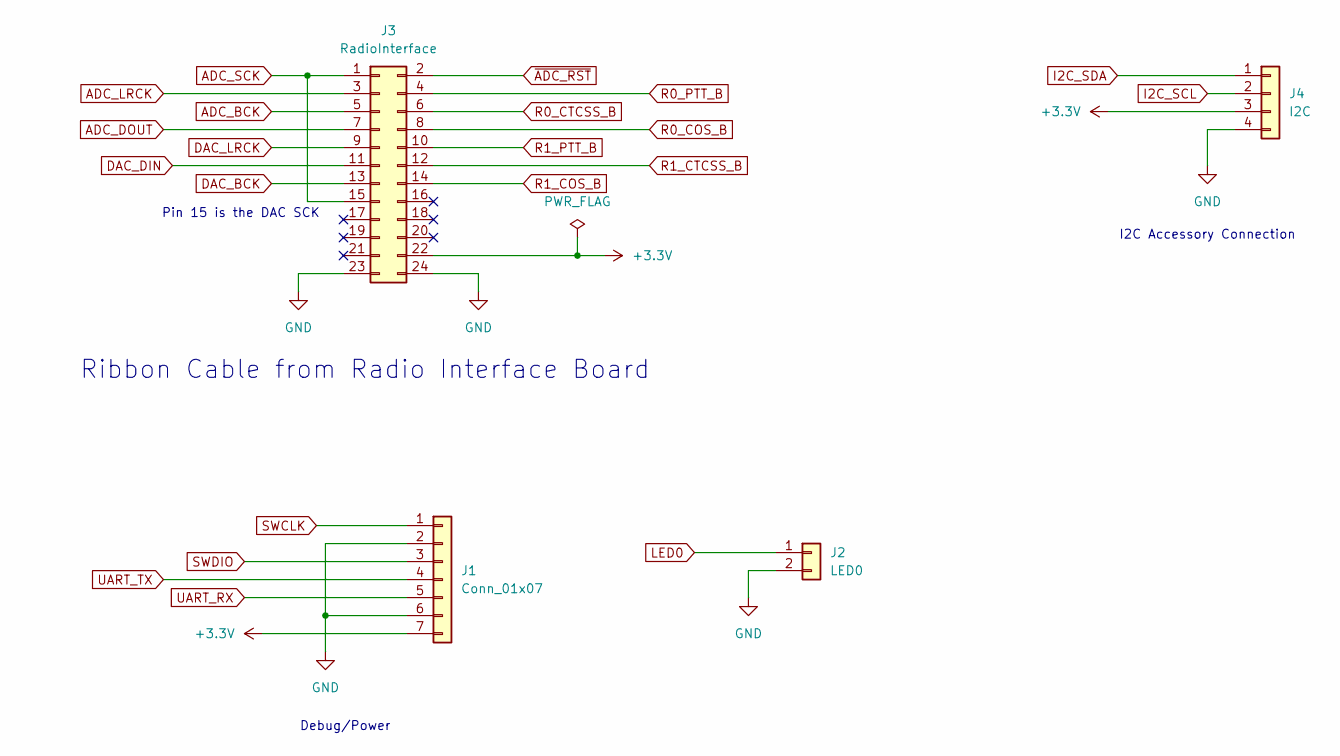
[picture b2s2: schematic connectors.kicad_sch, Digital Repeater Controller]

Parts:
J1: Conn_01x07; PinHeader_1x07_P2.54mm_Vertical
J2: LED0; PinHeader_1x02_P2.54mm_Vertical
J3: RadioInterface; PinHeader_2x12_P2.54mm_Vertical
J4: I2C; PinHeader_1x04_P2.54mm_Vertical

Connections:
+3.3V: J1.7, J3.22, J4.3; also elsewhere on the board
ADC_BCK: J3.5; also elsewhere on the board
ADC_DOUT: J3.7; also elsewhere on the board
ADC_LRCK: J3.3; also elsewhere on the board
ADC_SCK: J3.1, J3.15; also elsewhere on the board
DAC_BCK: J3.13; also elsewhere on the board
DAC_DIN: J3.11; also elsewhere on the board
DAC_LRCK: J3.9; also elsewhere on the board
GND: J1.2, J1.6, J2.2, J3.23, J3.24, J4.4; also elsewhere on the board
I2C_SCL: J4.2; also elsewhere on the board
I2C_SDA: J4.1; also elsewhere on the board
LED0: J2.1; also elsewhere on the board
R0_COS_B: J3.8; also elsewhere on the board
R0_CTCSS_B: J3.6; also elsewhere on the board
R0_PTT_B: J3.4; also elsewhere on the board
R1_COS_B: J3.14; also elsewhere on the board
R1_CTCSS_B: J3.12; also elsewhere on the board
R1_PTT_B: J3.10; also elsewhere on the board
SWCLK: J1.1; also elsewhere on the board
SWDIO: J1.3; also elsewhere on the board
UART_RX: J1.5; also elsewhere on the board
UART_TX: J1.4; also elsewhere on the board
~ADC_RST: J3.2; also elsewhere on the board

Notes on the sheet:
I2C Accessory Connection
Pin 15 is the DAC SCK
Ribbon Cable from Radio Interface Board
Debug/Power

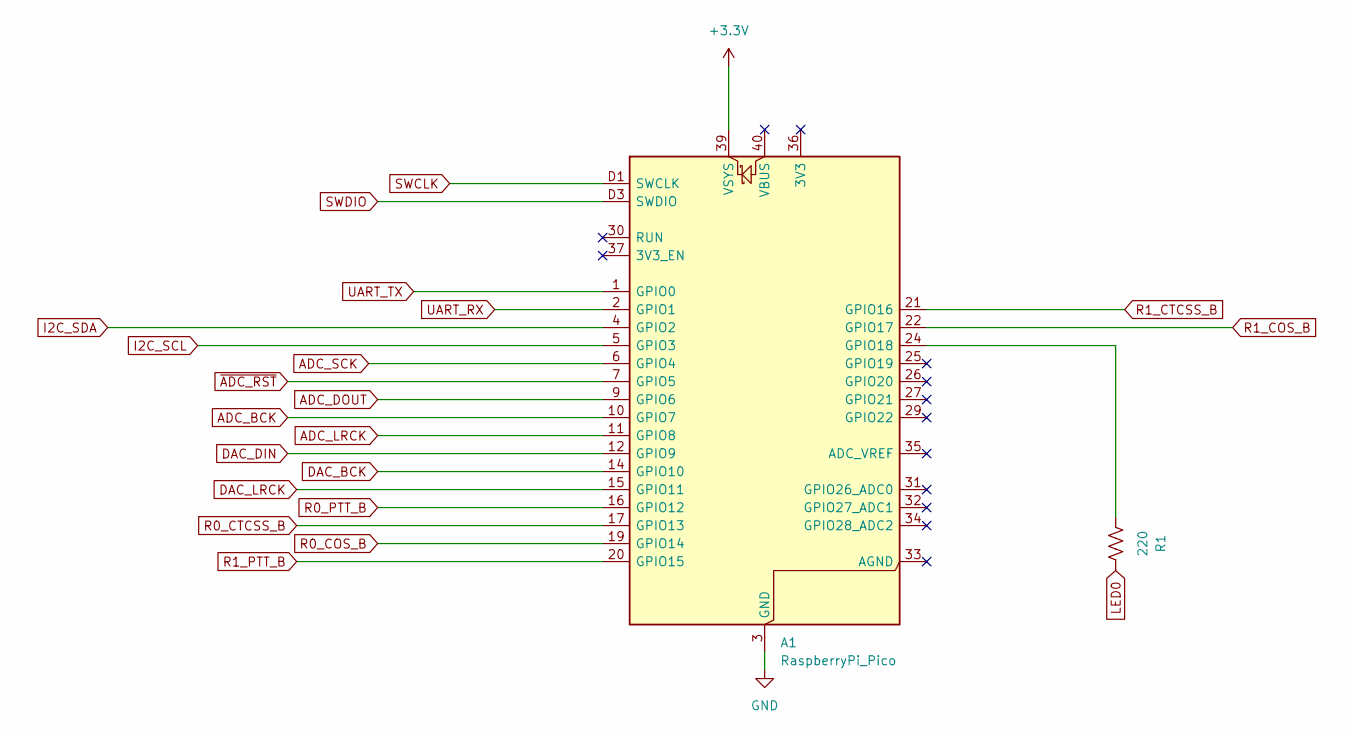
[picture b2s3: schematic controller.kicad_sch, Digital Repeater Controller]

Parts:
A1: RaspberryPi_Pico; RaspberryPi_Pico_SMD_HandSolder
R1: 220; R_0805_2012Metric_Pad1.20x1.40mm_HandSolder

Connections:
+3.3V: A1.39 (VSYS); also elsewhere on the board
ADC_BCK: A1.10 (GPIO7); also elsewhere on the board
ADC_DOUT: A1.9 (GPIO6); also elsewhere on the board
ADC_LRCK: A1.11 (GPIO8); also elsewhere on the board
ADC_SCK: A1.6 (GPIO4); also elsewhere on the board
DAC_BCK: A1.14 (GPIO10); also elsewhere on the board
DAC_DIN: A1.12 (GPIO9); also elsewhere on the board
DAC_LRCK: A1.15 (GPIO11); also elsewhere on the board
GND: A1.3 (GND), A1.8 (GND), A1.13 (GND), A1.18 (GND), A1.23 (GND), A1.28 (GND), A1.38 (GND), A1.D2 (GND); also elsewhere on the board
I2C_SCL: A1.5 (GPIO3); also elsewhere on the board
I2C_SDA: A1.4 (GPIO2); also elsewhere on the board
LED0: R1.2; also elsewhere on the board
unnamed: A1.24 (GPIO18), R1.1
R0_COS_B: A1.19 (GPIO14); also elsewhere on the board
R0_CTCSS_B: A1.17 (GPIO13); also elsewhere on the board
R0_PTT_B: A1.16 (GPIO12); also elsewhere on the board
R1_COS_B: A1.22 (GPIO17); also elsewhere on the board
R1_CTCSS_B: A1.21 (GPIO16); also elsewhere on the board
R1_PTT_B: A1.20 (GPIO15); also elsewhere on the board
SWCLK: A1.D1 (SWCLK); also elsewhere on the board
SWDIO: A1.D3 (SWDIO); also elsewhere on the board
UART_RX: A1.2 (GPIO1); also elsewhere on the board
UART_TX: A1.1 (GPIO0); also elsewhere on the board
~ADC_RST: A1.7 (GPIO5); also elsewhere on the board

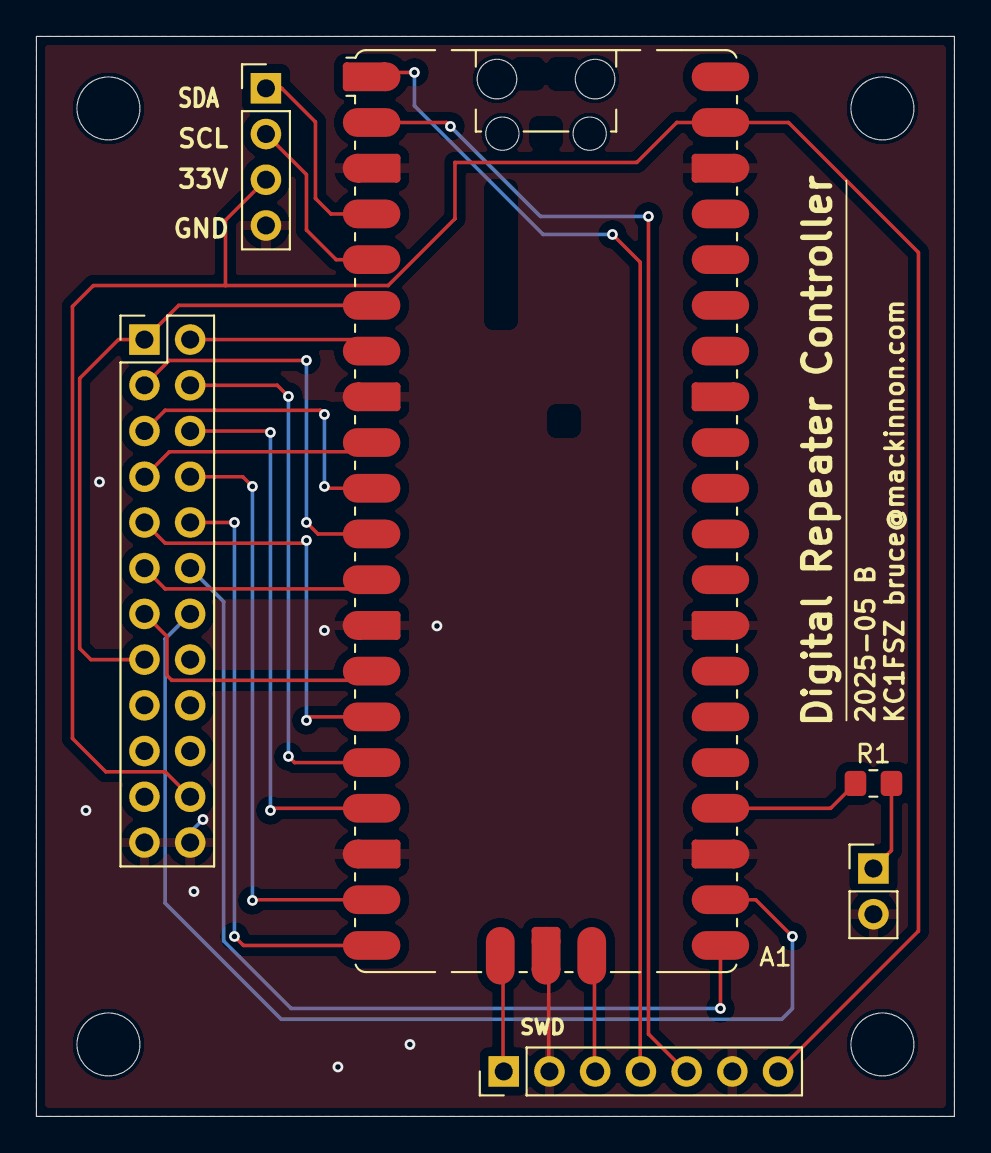
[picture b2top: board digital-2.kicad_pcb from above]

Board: 2 copper layers, 51.0 x 60.0 mm, 10 parts (0 on the bottom side), 24 nets.

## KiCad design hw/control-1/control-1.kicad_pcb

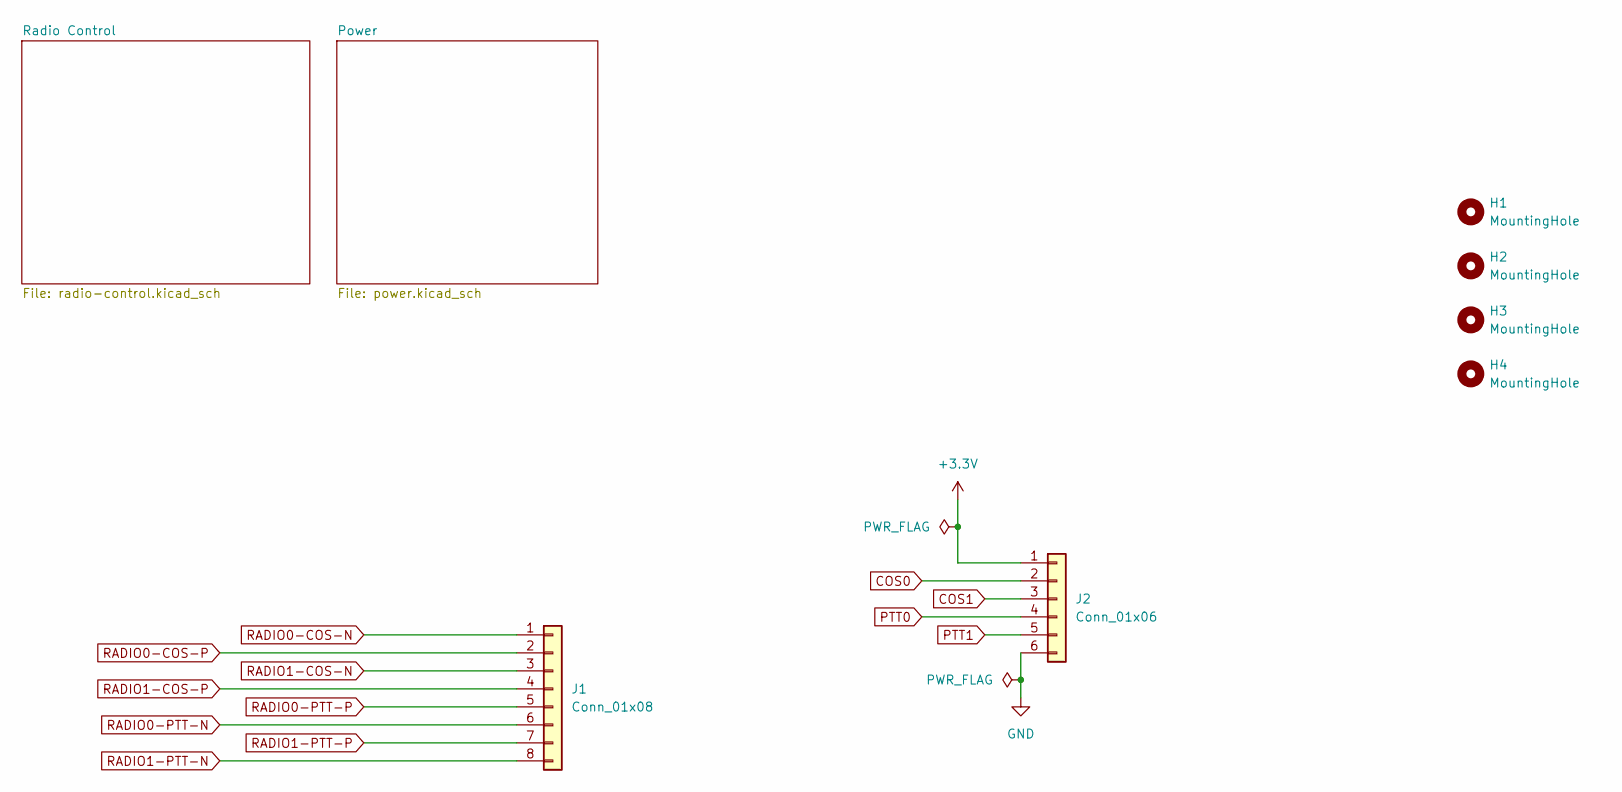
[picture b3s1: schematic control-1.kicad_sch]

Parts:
H1, H2, H3, H4: MountingHole; MountingHole_3.5mm
J1: Conn_01x08; PinHeader_1x08_P2.54mm_Vertical
J2: Conn_01x06; PinHeader_1x06_P2.54mm_Vertical

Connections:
+3.3V: J2.1; also elsewhere on the board
COS0: J2.2; also elsewhere on the board
COS1: J2.3; also elsewhere on the board
GND: J2.6; also elsewhere on the board
PTT0: J2.4; also elsewhere on the board
PTT1: J2.5; also elsewhere on the board
RADIO0-COS-N: J1.1; also elsewhere on the board
RADIO0-COS-P: J1.2; also elsewhere on the board
RADIO0-PTT-N: J1.6; also elsewhere on the board
RADIO0-PTT-P: J1.5; also elsewhere on the board
RADIO1-COS-N: J1.3; also elsewhere on the board
RADIO1-COS-P: J1.4; also elsewhere on the board
RADIO1-PTT-N: J1.8; also elsewhere on the board
RADIO1-PTT-P: J1.7; also elsewhere on the board

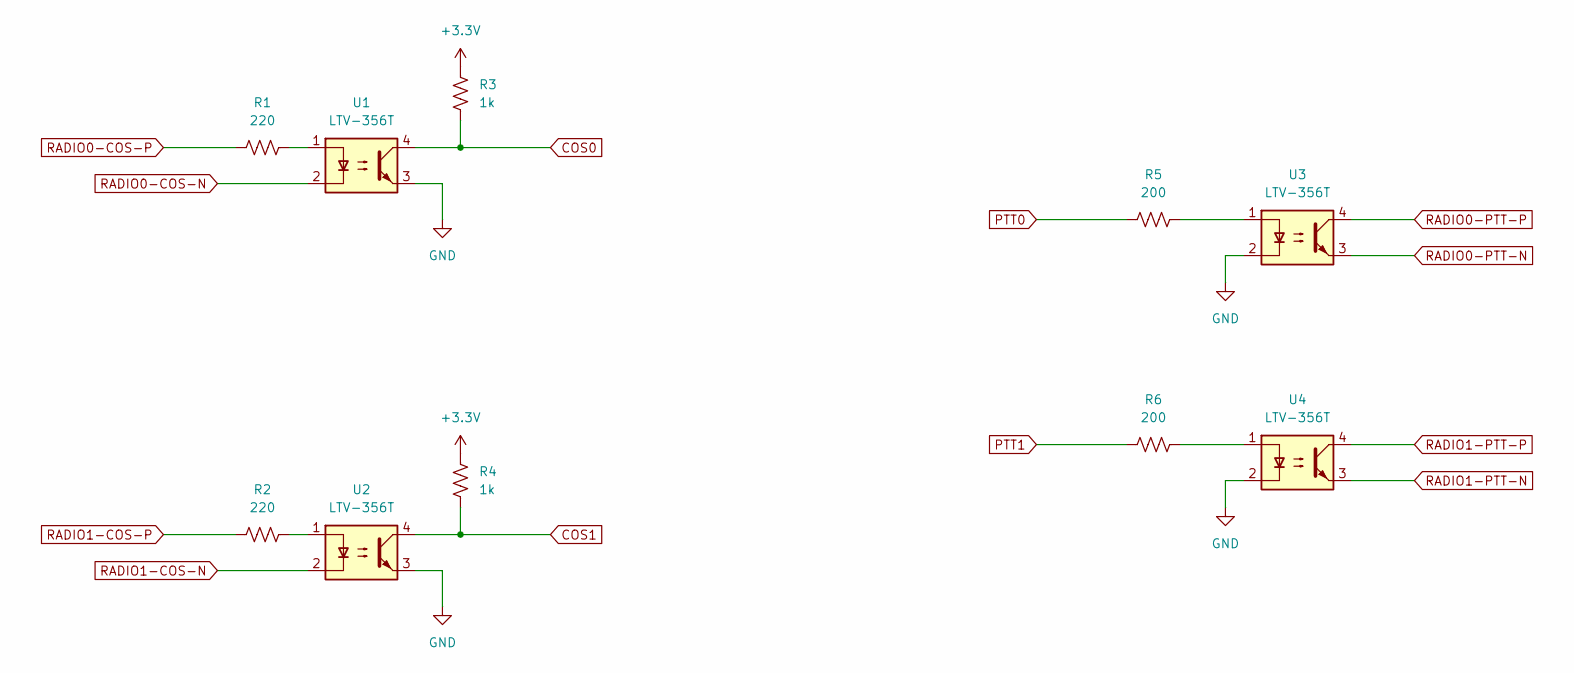
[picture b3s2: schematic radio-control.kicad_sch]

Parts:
R1, R2: 220; R_0805_2012Metric_Pad1.20x1.40mm_HandSolder
R3, R4: 1k; R_0805_2012Metric_Pad1.20x1.40mm_HandSolder
R5, R6: 200; R_0805_2012Metric_Pad1.20x1.40mm_HandSolder
U1, U2, U3, U4: LTV-356T; SO-4_4.4x3.6mm_P2.54mm

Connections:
+3.3V: R3.1, R4.1; also elsewhere on the board
COS0: R3.2, U1.4; also elsewhere on the board
COS1: R4.2, U2.4; also elsewhere on the board
GND: U1.3, U2.3, U3.2, U4.2; also elsewhere on the board
unnamed: R1.2, U1.1
unnamed: R2.2, U2.1
unnamed: R5.2, U3.1
unnamed: R6.2, U4.1
PTT0: R5.1; also elsewhere on the board
PTT1: R6.1; also elsewhere on the board
RADIO0-COS-N: U1.2; also elsewhere on the board
RADIO0-COS-P: R1.1; also elsewhere on the board
RADIO0-PTT-N: U3.3; also elsewhere on the board
RADIO0-PTT-P: U3.4; also elsewhere on the board
RADIO1-COS-N: U2.2; also elsewhere on the board
RADIO1-COS-P: R2.1; also elsewhere on the board
RADIO1-PTT-N: U4.3; also elsewhere on the board
RADIO1-PTT-P: U4.4; also elsewhere on the board

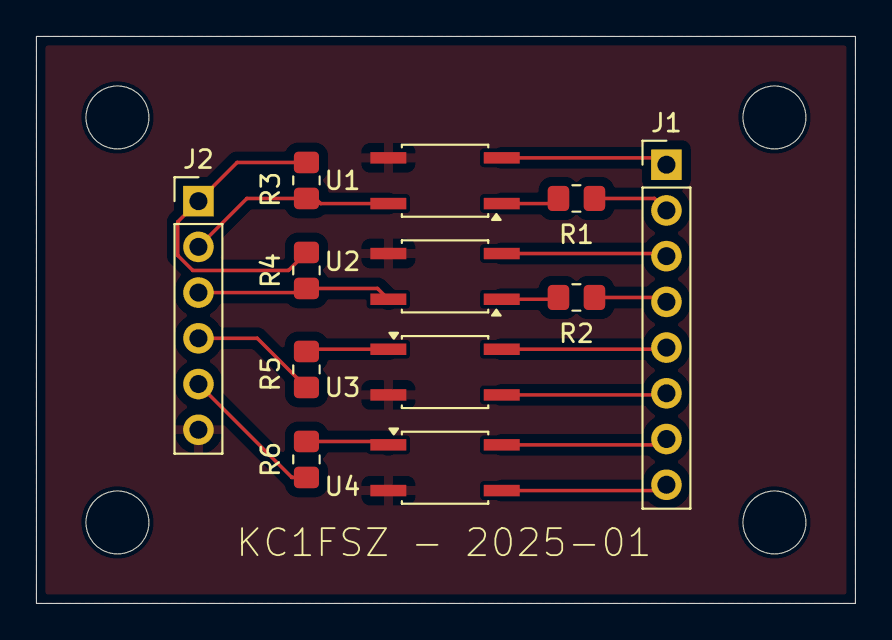
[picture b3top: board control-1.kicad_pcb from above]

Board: 2 copper layers, 45.5 x 31.5 mm, 16 parts (0 on the bottom side), 18 nets.

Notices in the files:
main.cpp:
Copyright (C) 2025, Bruce MacKinnon KC1FSZ
This program is free software: you can redistribute it and/or modify
it under the terms of the GNU General Public License as published by
the Free Software Foundation, either version 3 of the License, or
(at your option) any later version.
hw/if-2/connectors.kicad_sch:
Copyright (C) Bruce MacKinnon, 2025
